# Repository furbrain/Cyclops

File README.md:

# Cyclops

Cave surveying with a camera and IMU. Under development

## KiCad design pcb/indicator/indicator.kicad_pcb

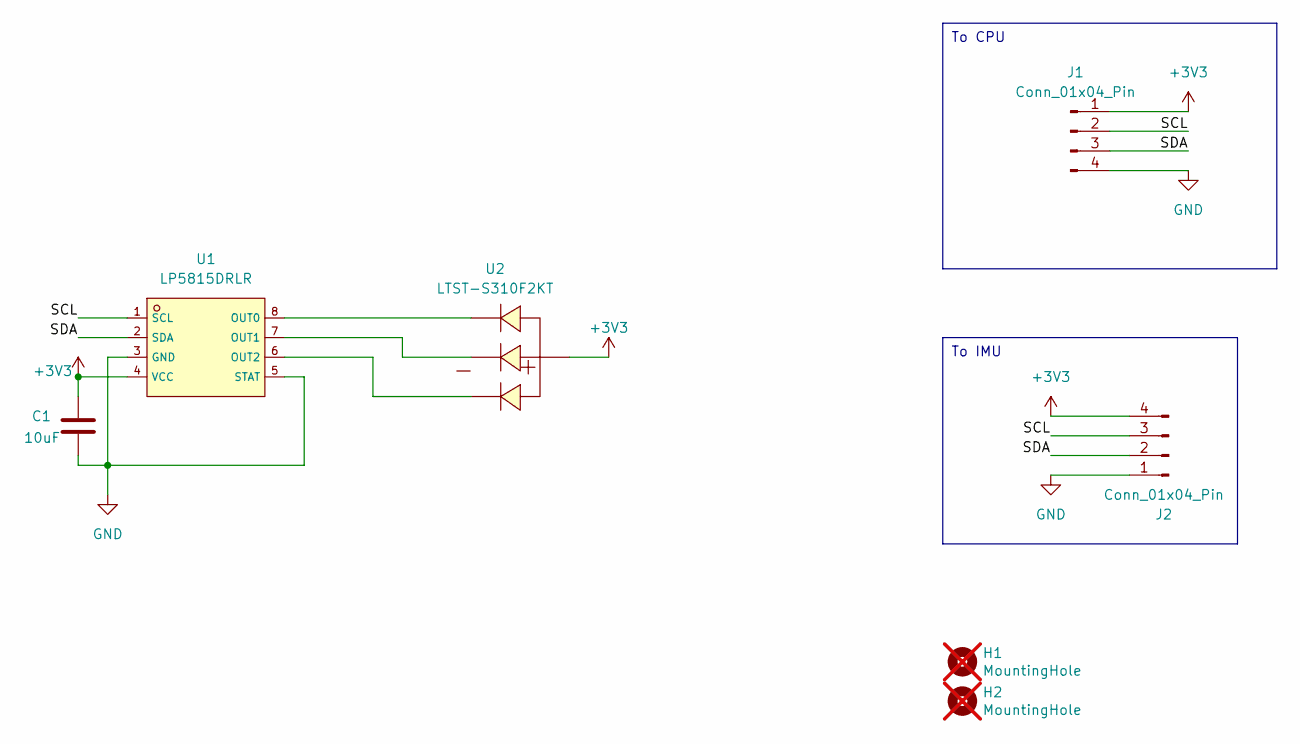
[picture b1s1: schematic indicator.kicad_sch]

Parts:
C1: 10uF; C_0805_2012Metric; JLCPCB C117956
H1, H2: MountingHole; MountingHole_3.2mm_M3; Part Description M2.5 mounting hole; not fitted
J1, J2: Conn_01x04_Pin; JUSHUO_AFA07-S04FCA-00_1x4-1MP_P1.0mm_Horizontal; JLCPCB C262710
U1: LP5815DRLR; SOT-583-8_L2.1-W1.2-P0.50-LS1.6-BL; JLCPCB C47262831
U2: LTST-S310F2KT; LED-SMD_4P-L3.2-W1.5_LTST-S310F2KT; JLCPCB C284950

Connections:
+3V3: C1.1, J1.1, J2.4, U1.4 (VCC), U2.4 (A)
/SCL: J1.2, J2.3, U1.1 (SCL)
/SDA: J1.3, J2.2, U1.2 (SDA)
GND: C1.2, J1.4, J2.1, U1.3 (GND), U1.5 (STAT)
unnamed: U1.8 (OUT0), U2.1 (C1)
unnamed: U1.7 (OUT1), U2.2 (C2)
unnamed: U1.6 (OUT2), U2.3 (C3)

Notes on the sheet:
To CPU
To IMU

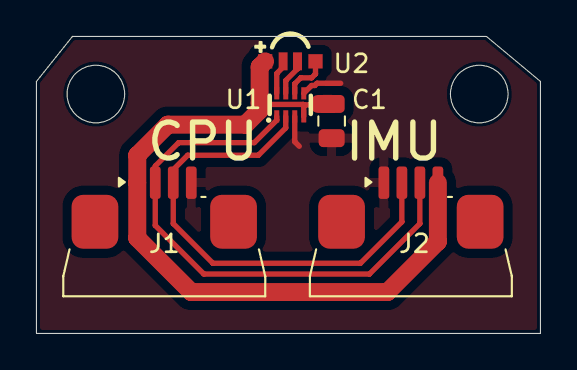
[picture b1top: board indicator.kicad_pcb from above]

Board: 2 copper layers, 28.0 x 16.5 mm, 7 parts (0 on the bottom side), 7 nets.

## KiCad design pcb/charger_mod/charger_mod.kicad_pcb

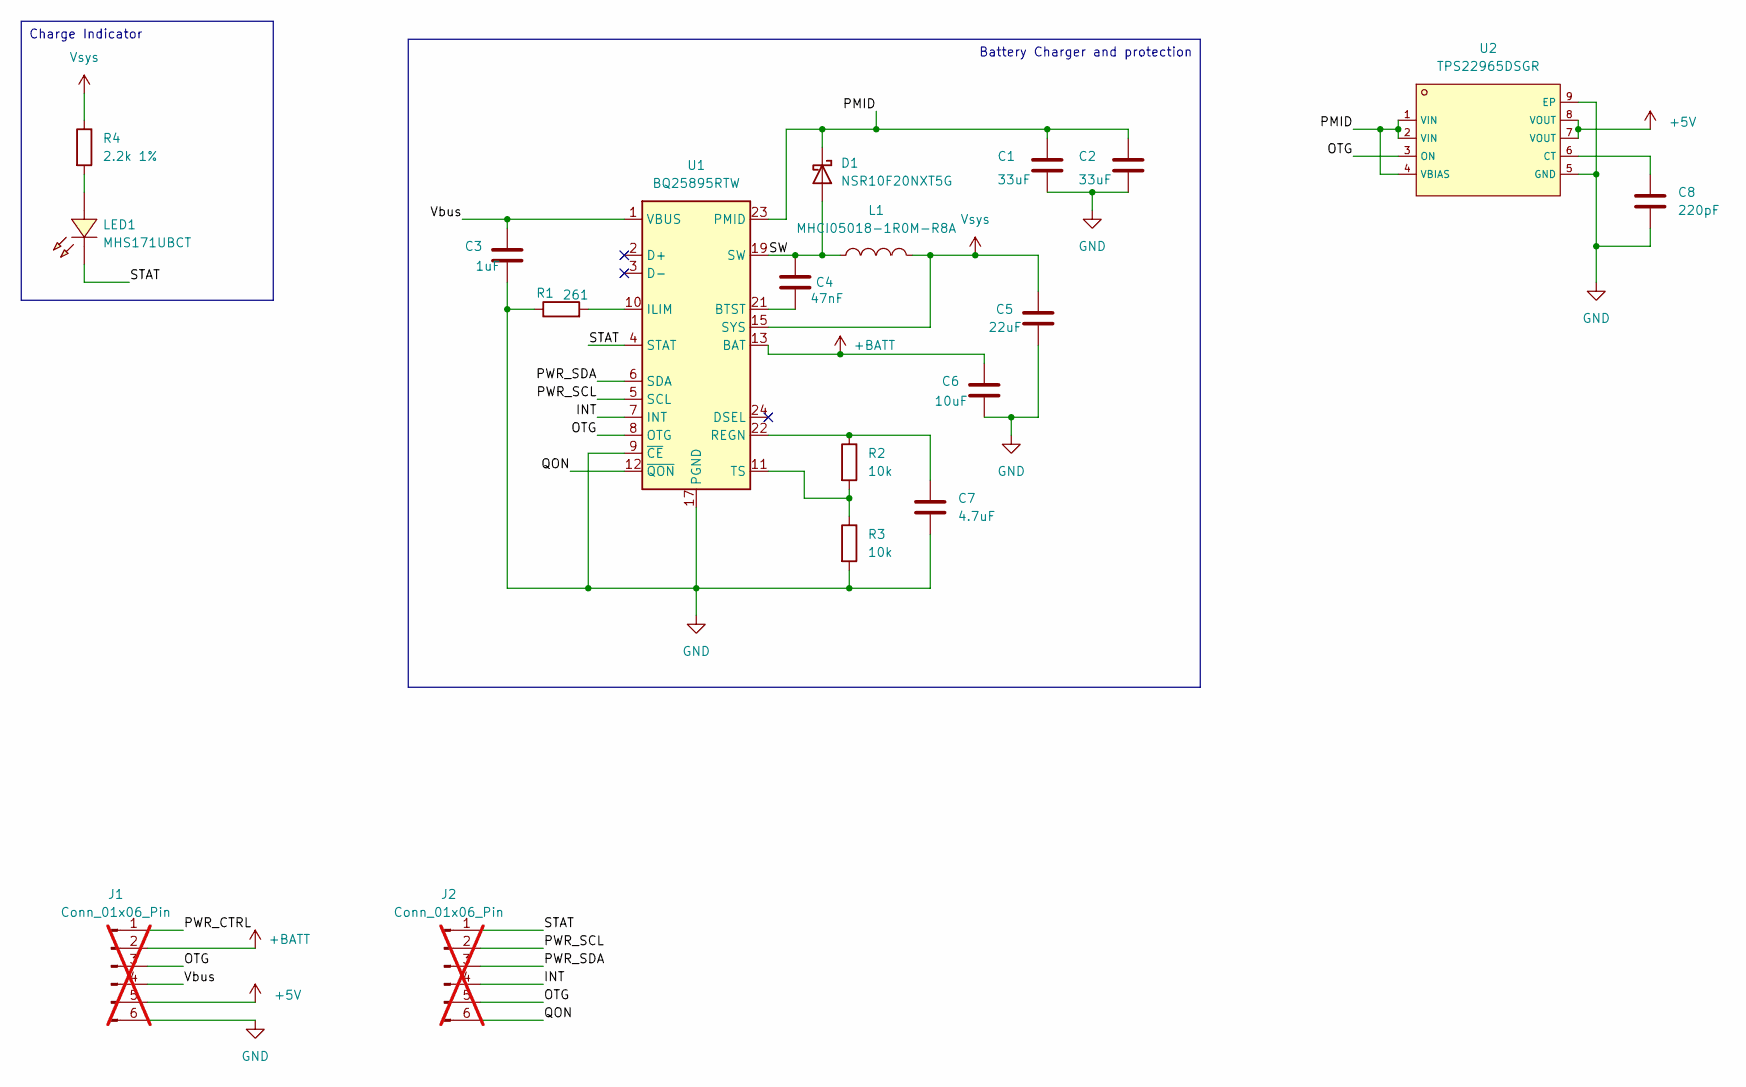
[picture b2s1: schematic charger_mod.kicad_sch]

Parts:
C1, C2: 33uF; C_1206_3216Metric; LCSC PN C76658
C3: 1uF; C_0603_1608Metric; LCSC PN C1592
C4: 47nF; C_0402_1005Metric; LCSC PN C106260
C5: 22uF; C_0805_2012Metric; LCSC PN C45783
C6: 10uF; C_0805_2012Metric; LCSC PN C117956
C7: 4.7uF; C_0603_1608Metric; LCSC PN C19666
C8: 220pF; C_0402_1005Metric; JLCPCB C1530
D1: NSR10F20NXT5G; Nexperia_DSN1608-2_1.6x0.8mm; LCSC PN C893809
J1, J2: Conn_01x06_Pin; PinHeader_1x06_P2.54mm_Vertical; not fitted
L1: MHCI05018-1R0M-R8A; IND-SMD_L5.7-W5.4; LCSC PN C329539
LED1: MHS171UBCT; LED-SMD_L2.1-W1.0-R-RD; LCSC PN C693906
R1: 261; R_0402_1005Metric; LCSC PN C25097
R2, R3: 10k; R_0402_1005Metric; LCSC PN C25744
R4: 2.2k 1%; R_0402_1005Metric; LCSC PN C25879
U1: BQ25895RTW; Texas_RTW_WQFN-24-1EP_4x4mm_P0.5mm_EP2.7x2.7mm_ThermalVias; LCSC PN C80200
U2: TPS22965DSGR; UDFN-8_L2.0-W2.0-P0.50-TL-EP; LCSC C122837

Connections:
+5V: J1.5, U2.7 (VOUT), U2.8 (VOUT)
+BATT: C6.1, J1.2, U1.13 (BAT), U1.14 (BAT)
/INT: J2.4, U1.7 (INT)
/OTG: J1.3, J2.5, U1.8 (OTG), U2.3 (ON)
/PMID: C1.1, C2.1, D1.1 (K), U1.23 (PMID), U2.1 (VIN), U2.2 (VIN), U2.4 (VBIAS)
/PWR_CTRL: J1.1
/PWR_SCL: J2.2, U1.5 (SCL)
/PWR_SDA: J2.3, U1.6 (SDA)
/QON: J2.6, U1.12 (~QON)
/STAT: J2.1, LED1.2 (K), U1.4 (STAT)
/SW: C4.1, D1.2 (A), L1.1, U1.19 (SW), U1.20 (SW)
/Vbus: C3.1, J1.4, U1.1 (VBUS)
GND: C1.2, C2.2, C3.2, C5.2, C6.2, C7.2, C8.2, J1.6, R1.1, R3.2, U1.9 (~CE), U1.17 (PGND), U1.18 (PGND), U1.25 (PGND), U2.5 (GND), U2.9 (EP)
unnamed: LED1.1 (A), R4.2
unnamed: C4.2, U1.21 (BTST)
unnamed: R1.2, U1.10 (ILIM)
unnamed: C7.1, R2.1, U1.22 (REGN)
unnamed: R2.2, R3.1, U1.11 (TS)
unnamed: C8.1, U2.6 (CT)
Vsys: C5.1, L1.2, R4.1, U1.15 (SYS), U1.16 (SYS)

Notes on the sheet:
Battery Charger and protection
Charge Indicator

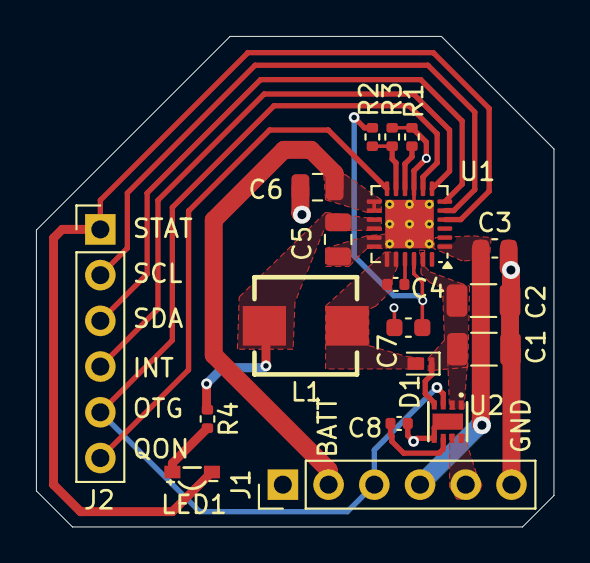
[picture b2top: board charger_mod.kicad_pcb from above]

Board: 2 copper layers, 28.8 x 27.2 mm, 19 parts (0 on the bottom side), 19 nets.

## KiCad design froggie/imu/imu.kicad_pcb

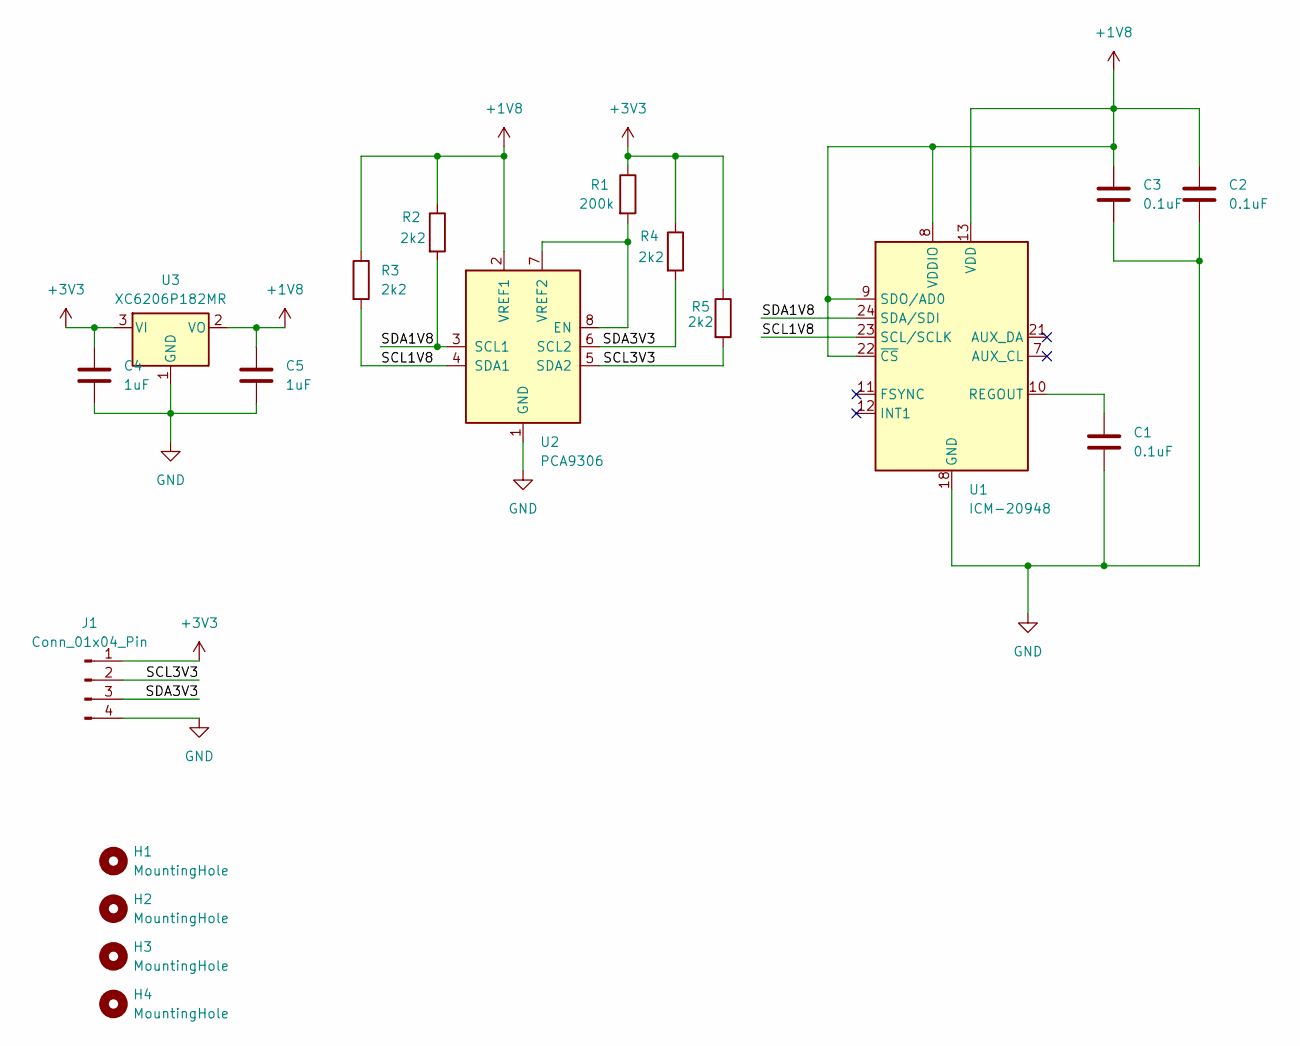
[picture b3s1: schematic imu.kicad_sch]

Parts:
C1, C2, C3: 0.1uF; C_0402_1005Metric
C4, C5: 1uF; C_0402_1005Metric
H1, H2, H3, H4: MountingHole; MountingHole_2.2mm_M2
J1: Conn_01x04_Pin; JUSHUO_AFA07-S04FCA-00_1x4-1MP_P1.0mm_Horizontal; JLCPCB C262710
R1: 200k; R_0402_1005Metric
R2, R3, R4, R5: 2k2; R_0402_1005Metric
U1: ICM-20948; InvenSense_QFN-24_3x3mm_P0.4mm
U2: PCA9306; VSSOP-8_2.3x2mm_P0.5mm
U3: XC6206P182MR; SOT-23-3; JLCPCB No C21659

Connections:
+1V8: C2.1, C3.1, C5.1, R2.1, R3.1, U1.8 (VDDIO), U1.9 (SDO/AD0), U1.13 (VDD), U1.22 (~CS), U2.2 (VREF1), U3.2 (VO)
+3V3: C4.1, J1.1, R1.1, R4.1, R5.1, U3.3 (VI)
/SCL1V8: R3.2, U1.23 (SCL/SCLK), U2.4 (SDA1)
/SCL3V3: J1.2, R5.2, U2.5 (SDA2)
/SDA1V8: R2.2, U1.24 (SDA/SDI), U2.3 (SCL1)
/SDA3V3: J1.3, R4.2, U2.6 (SCL2)
GND: C1.2, C2.2, C3.2, C4.2, C5.2, J1.4, U1.18 (GND), U1.20 (GND), U2.1 (GND), U3.1 (GND)
unnamed: C1.1, U1.10 (REGOUT)
unnamed: R1.2, U2.7 (VREF2), U2.8 (EN)

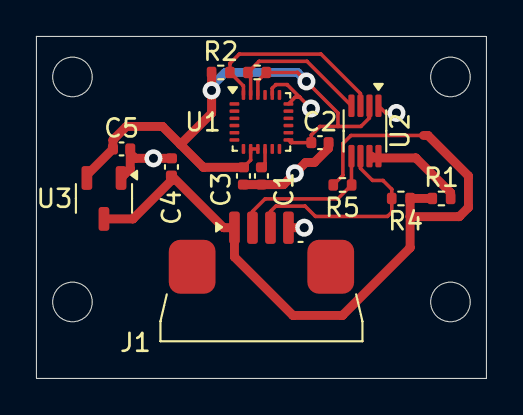
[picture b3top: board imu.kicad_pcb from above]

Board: 2 copper layers, 25.0 x 19.0 mm, 18 parts (0 on the bottom side), 9 nets.

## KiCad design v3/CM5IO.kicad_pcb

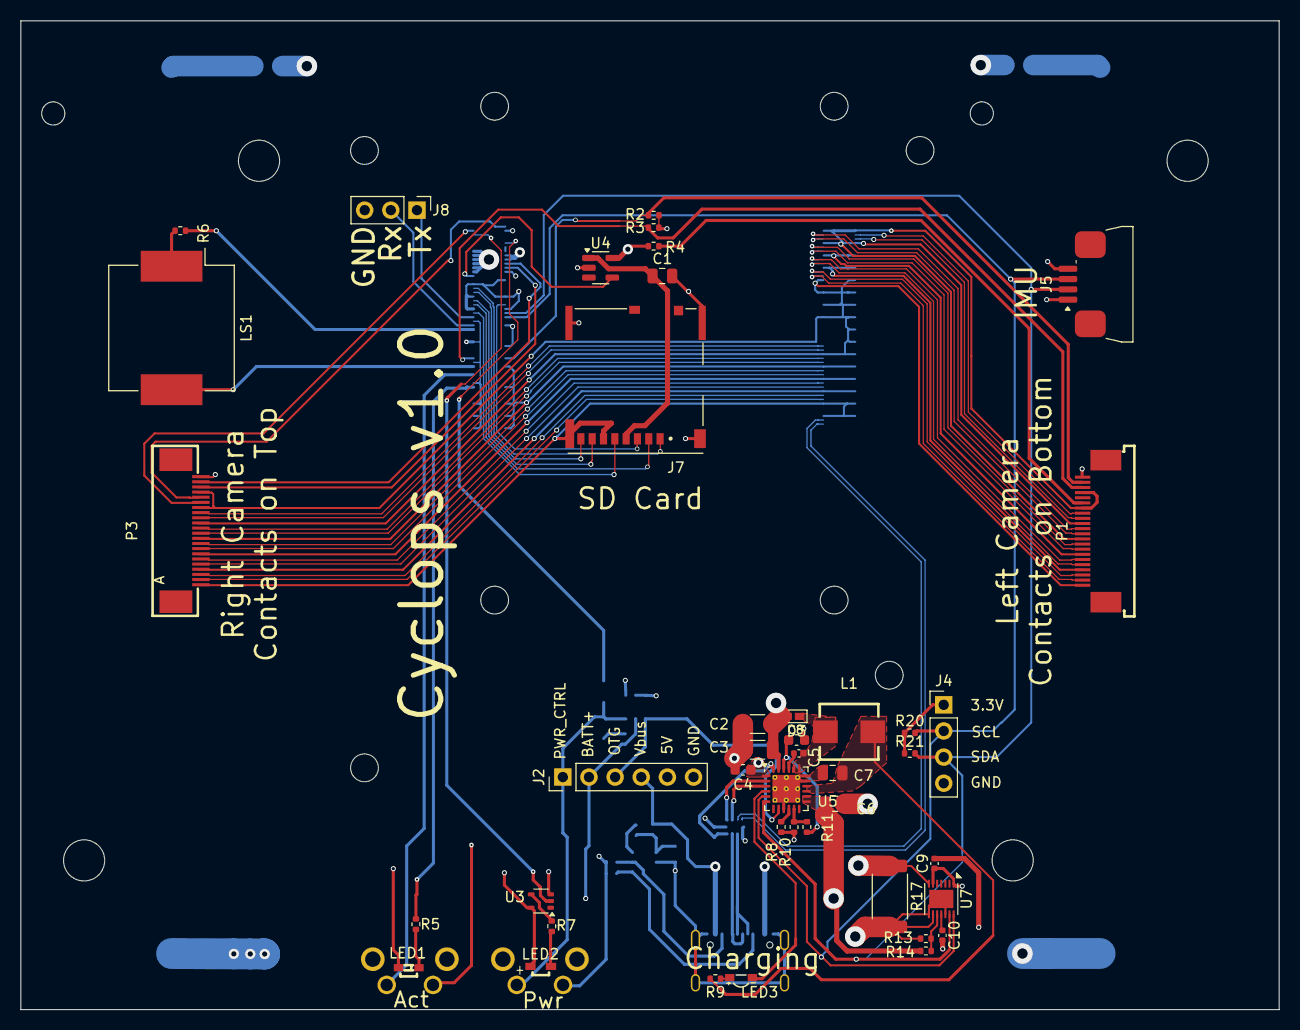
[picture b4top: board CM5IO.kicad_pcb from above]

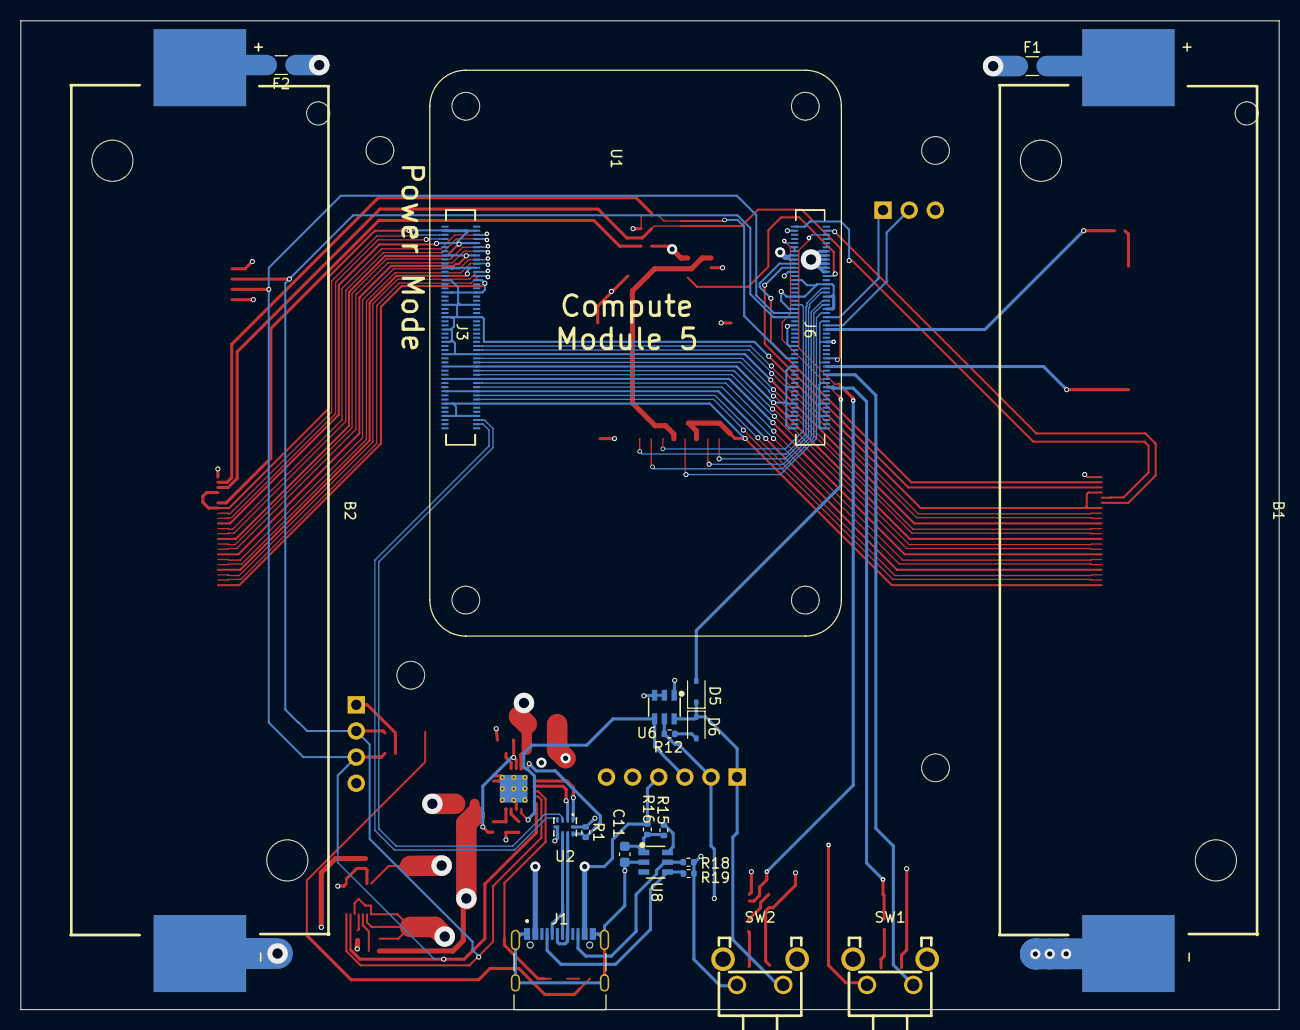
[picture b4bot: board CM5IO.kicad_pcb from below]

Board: 4 copper layers, 122.3 x 96.1 mm, 68 parts (22 on the bottom side), 82 nets.

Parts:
B1, B2: BH-21700-B1BJ001; BAT-SMD_L82.5.5-W25-BH-21700-B1BJ001
C1, C7: 10uF; C_0805_2012Metric
C2, C3: 33uF; C_1206_3216Metric
C4, C11: 1uF; C_0603_1608Metric
C5: 47nF; C_0402_1005Metric
C6: 22uF; C_0805_2012Metric
C8: 4.7uF; C_0603_1608Metric
C9: 100nF; C_0402_1005Metric
C10: 470nF; C_0402_1005Metric
D3: NSR10F20NXT5G; Nexperia_DSN1608-2_1.6x0.8mm
D5, D6: D_Schottky; D_SOD-323
F1, F2: Fuse; Fuse_1206_3216Metric
H1, H2, H3, H4: MountingHole; MountingHole_2.7mm_M2.5_DIN965
J1: TYPE-C-31-M-12; HRO_TYPE-C-31-M-12
J2: Conn_01x06_Pin; PinHeader_1x06_P2.54mm_Vertical
J3, J6: 10164227-1001A1RLF; CM5_connector
J4: Conn_01x04_Pin; PinHeader_1x04_P2.54mm_Vertical
J5: Conn_01x04_Pin; JUSHUO_AFA07-S04FCA-00_1x4-1MP_P1.0mm_Horizontal
J7: Micro_SD_Card_Det; SDCARD_MOLEX_503398-1892
J8: UART Connection; PinHeader_1x03_P2.54mm_Vertical
L1: MHCI05018-1R0M-R8A; IND-SMD_L5.7-W5.4
LED1: MHS171CYCT; LED-SMD_L2.0-W1.1-R-RD-SIDE_YELLOW
LED2: MHS171UGCT; LED-SMD_L2.0-W1.1_RD_GREEN_SIDE
LED3: MHS171UBCT; LED-SMD_L2.1-W1.0-R-RD
LS1: KMTG1203; Buzzer_Mallory_AST1240MLQ
P1: AFC07-S22FCC-00 (Bottom contact); FPC-SMD_AFC07-S22FCC-00
P3: FPC_0_5MM_22P_Pull_type_H2_0mm_Pick_up; FPC-SMD_P0.50-22P_LSSJ-H2.0-22P
R1, R10, R11, R12, R15: 10k; R_0402_1005Metric
R2, R3, R4, R20, R21: 2.2K 1%; R_0402_1005Metric
R5, R7, R16: 1k; R_0402_1005Metric
R6: 180; R_0402_1005Metric
R8: 261; R_0402_1005Metric
R9: 2.2k 1%; R_0402_1005Metric
R13: 300k; R_0402_1005Metric
R14: 200k; R_0402_1005Metric
R17: 10mOhm; R_2512_6332Metric
R18, R19: 5.1k; R_0402_1005Metric
SW1: TS-1093C-A14B3-D1; SW-TH_TS-1093C-A14B3-D1
SW2: TS-1093C-A5B3-D1; SW-TH_TS-1093C-A5B3-D1
U1: Raspberry-Pi-5-Compute-Module
U2: TS3USB221ARSER; UQFN-10_L2.0-W1.5-P0.50-BL
U3: 74LVC1G07SE-7; SOT-353_SC-70-5
U4: RT9742GGJ5; SOT-23-5
U5: BQ25895RTW; Texas_RTW_WQFN-24-1EP_4x4mm_P0.5mm_EP2.7x2.7mm_ThermalVias
U6: SN74LVC1G57DBVR; SOT-23-6_L2.9-W1.6-P0.95-LS2.8-BL
U7: MAX17261xxTD; TDFN-14-1EP_3x3mm_P0.4mm_EP1.78x2.35mm
U8: CH221K; SOT-23-6_L2.9-W1.6-P0.95-LS2.8-BL-2

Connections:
+BATT: C7.1, C9.1, F1.1, F2.1, J2.2, R12.1, R13.1, U5.13 (BAT), U5.14 (BAT), U6.5 (VCC), U7.1 (TH), U7.6 (BATT)
-BATT: B1.2, B2.2, C9.2, C10.2, R14.2, R17.2, U7.8 (GND), U7.9 (CSPL), U7.12 (ALRT), U7.15 (GND)
/+3.3v: J4.1, J5.4, J6.78 (GPIO_VREF(1.8v/3.3v_Input)), J6.84 (+3.3v_(Output)), J6.86 (+3.3v_(Output)), LED1.1 (K), LED2.1 (+), P1.1, P3.1, R1.1, R2.1, R3.1, R4.1, R20.1, R21.1, U2.10 (VCC), U3.5 (VCC), U4.5 (IN), U6.1 (IN1)
/CC1: J1.A5 (CC1), R19.1, U8.4 (CC1)
/CC2: J1.B5 (CC2), R18.2, U8.5 (CC2)
/CM5_5V: C2.1, C3.1, D3.1 (K), J2.5, J6.77 (+5v_(Input)), J6.79 (+5v_(Input)), J6.81 (+5v_(Input)), J6.83 (+5v_(Input)), J6.85 (+5v_(Input)), J6.87 (+5v_(Input)), U5.23 (PMID)
/CM5_GPIO ( Ethernet, GPIO, SDCARD)/+1.8v: J6.88 (+1.8v_(Output)), J6.90 (+1.8v_(Output))
/CM5_GPIO ( Ethernet, GPIO, SDCARD)/BUTTON: J6.27 (GPIO20), SW1.2
/CM5_GPIO ( Ethernet, GPIO, SDCARD)/BUZZ_A: J6.49 (GPIO18), R6.1
/CM5_GPIO ( Ethernet, GPIO, SDCARD)/BUZZ_B: J6.31 (GPIO12), LS1.2
/CM5_GPIO ( Ethernet, GPIO, SDCARD)/CAM_GPIO0: J6.97 (CAM_GPIO0), P3.6
/CM5_GPIO ( Ethernet, GPIO, SDCARD)/CAM_GPIO1: J6.100 (CAM_GPIO1), P3.5
/CM5_GPIO ( Ethernet, GPIO, SDCARD)/GPIO14: J6.55 (GPIO14), J8.1
/CM5_GPIO ( Ethernet, GPIO, SDCARD)/GPIO15: J6.51 (GPIO15), J8.2
/CM5_GPIO ( Ethernet, GPIO, SDCARD)/ID_SC: J6.35 (ID_SC), P1.3, R3.2
/CM5_GPIO ( Ethernet, GPIO, SDCARD)/ID_SD: J6.36 (ID_SD), P1.2, R2.2
/CM5_GPIO ( Ethernet, GPIO, SDCARD)/SD_CLK: J6.57 (SD_CLK), J7.5 (CLK)
/CM5_GPIO ( Ethernet, GPIO, SDCARD)/SD_CMD: J6.62 (SD_CMD), J7.3 (CMD)
/CM5_GPIO ( Ethernet, GPIO, SDCARD)/SD_DAT0: J6.63 (SD_DAT0), J7.7 (DAT0)
/CM5_GPIO ( Ethernet, GPIO, SDCARD)/SD_DAT1: J6.67 (SD_DAT1), J7.8 (DAT1)
/CM5_GPIO ( Ethernet, GPIO, SDCARD)/SD_DAT2: J6.69 (SD_DAT2), J7.1 (DAT2)
/CM5_GPIO ( Ethernet, GPIO, SDCARD)/SD_DAT3: J6.61 (SD_DAT3), J7.2 (DAT3/CD)
/CM5_GPIO ( Ethernet, GPIO, SDCARD)/SD_PWR: C1.1, J7.4 (VDD), U4.1 (OUT)
/CM5_GPIO ( Ethernet, GPIO, SDCARD)/SD_PWR_ON: J6.75 (SD_PWR_ON), U4.4 (EN)
/CM5_GPIO ( Ethernet, GPIO, SDCARD)/nPWR_LED: J6.95 (LED_nPWR), U3.2
/CM5_HighSpeed/DPHY0_C_N: J3.27 (MIPI0_C_N), P3.15
/CM5_HighSpeed/DPHY0_C_P: J3.29 (MIPI0_C_P), P3.14
/CM5_HighSpeed/DPHY0_D0_N: J3.15 (MIPI0_D0_N), P3.21
/CM5_HighSpeed/DPHY0_D0_P: J3.17 (MIPI0_D0_P), P3.20
/CM5_HighSpeed/DPHY0_D1_N: J3.21 (MIPI0_D1_N), P3.18
/CM5_HighSpeed/DPHY0_D1_P: J3.23 (MIPI0_D1_P), P3.17
/CM5_HighSpeed/DPHY0_D2_N: J3.33 (MIPI0_D2_N), P3.12
/CM5_HighSpeed/DPHY0_D2_P: J3.35 (MIPI0_D2_P), P3.11
/CM5_HighSpeed/DPHY0_D3_N: J3.39 (MIPI0_D3_N), P3.9
/CM5_HighSpeed/DPHY0_D3_P: J3.41 (MIPI0_D3_P), P3.8
/CM5_HighSpeed/DPHY1_C_N: J3.87 (MIPI1_C_N), P1.15
/CM5_HighSpeed/DPHY1_C_P: J3.89 (MIPI1_C_P), P1.14
/CM5_HighSpeed/DPHY1_D0_N: J3.75 (MIPI1_D0_N), P1.21
/CM5_HighSpeed/DPHY1_D0_P: J3.77 (MIPI1_D0_P), P1.20
/CM5_HighSpeed/DPHY1_D1_N: J3.81 (MIPI1_D1_N), P1.18
/CM5_HighSpeed/DPHY1_D1_P: J3.83 (MIPI1_D1_P), P1.17
/CM5_HighSpeed/DPHY1_D2_N: J3.93 (MIPI1_D2_N), P1.12
/CM5_HighSpeed/DPHY1_D2_P: J3.95 (MIPI1_D2_P), P1.11
/CM5_HighSpeed/DPHY1_D3_N: J3.94 (MIPI1_D3_N), P1.9
/CM5_HighSpeed/DPHY1_D3_P: J3.96 (MIPI1_D3_P), P1.8
/CM5_HighSpeed/SCL0: J6.80 (SCL0), P3.3
/CM5_HighSpeed/SDA0: J6.82 (SDA0), P3.2
/CM5_USB2_N: J3.3 (USB2_N), U2.4 (2D-)
/CM5_USB2_P: J3.5 (USB2_P), U2.3 (2D+)
/DSEL: R1.2, U2.9 (S), U5.24 (DSEL)
/PWR_BUT: D5.2 (A), J6.92 (PWR_BUT)
/PWR_D+: U2.1 (1D+), U5.2 (D+)
/PWR_D-: U2.2 (1D-), U5.3 (D-)
/PWR_SCL: J4.2, J5.3, J6.56 (GPIO3), R20.2, U5.5 (SCL), U7.14 (SCL)
/PWR_SDA: J4.3, J5.2, J6.58 (GPIO2), R21.2, U5.6 (SDA), U7.13 (SDA)
/Power/OTG: J2.3, U5.8 (OTG), U6.4 (Y)
/Power/PWR_CTRL: D5.1 (K), D6.1 (K), J2.1, SW2.2, U6.6 (IN2)
/Power/STAT: LED3.2 (K), U5.4 (STAT)
/Power/SW: C5.1, D3.2 (A), L1.1, U5.19 (SW), U5.20 (SW)
/USB2_N: J1.A7 (DN1), J1.B7 (DN2), U2.7 (D-)
/USB2_P: J1.A6 (DP1), J1.B6 (DP2), U2.8 (D+)
/Vbus: C4.1, J1.A4_B9 (VBUS), J1.B4_A9 (VBUS), J2.4, R16.1, U5.1 (VBUS)
GND: C1.2, C2.2, C3.2, C4.2, C6.2, C7.2, C8.2, C11.2, J1.A1_B12 (GND), J1.B1_A12 (GND), J1.S1 (SHIELD), J1.S2 (SHIELD), J1.S3 (SHIELD), J1.S4 (SHIELD), J2.6, J3.7 (GND), J3.8 (GND), J3.13 (GND), J3.14 (GND), J3.19 (GND), J3.20 (GND), J3.25 (GND), J3.26 (GND), J3.31 (GND), J3.32 (GND), J3.37 (GND), J3.38 (GND), J3.44 (GND), J3.50 (GND), J3.55 (GND), J3.56 (GND), J3.61 (GND), J3.62 (GND), J3.67 (GND), J3.68 (GND), J3.73 (GND), J3.74 (GND), J3.79 (GND), J3.80 (GND), J3.85 (GND), J3.86 (GND), J3.91 (GND), J3.92 (GND), J3.97 (GND), J3.98 (GND), J4.4, J5.1, J6.1 (GND), J6.2 (GND), J6.7 (GND), J6.8 (GND), J6.13 (GND), J6.14 (GND), J6.22 (GND), J6.23 (GND), J6.32 (GND), J6.33 (GND), J6.42 (GND), J6.43 (GND), J6.52 (GND), J6.53 (GND), J6.59 (GND), J6.60 (GND), J6.65 (GND), J6.66 (GND), J6.71 (GND), J6.74 (GND), J6.98 (GND), J7.6 (VSS), J7.11 (SHIELD), J8.3, P1.4, P1.7, P1.10, P1.13, P1.16, P1.19, P1.22, P3.4, P3.7, P3.10, P3.13, P3.16, P3.19, P3.22, R8.1, R11.2, R17.1, R18.1, R19.2, SW1.1, SW2.1, U2.5 (GND), U2.6 (OE#), U3.3 (GND), U4.2 (GND), U5.9 (~CE), U5.17 (PGND), U5.18 (PGND), U5.25 (PGND), U6.2 (GND), U6.3 (IN0), U7.7 (CSN), U8.2 (GND)
unnamed: B1.1, F1.2
unnamed: B2.1, F2.2
unnamed: D6.2 (A), R12.2
unnamed: J6.21 (LED_nACT), R5.2
unnamed: LED1.2 (A), R5.1
unnamed: LED2.2 (-), R7.1
unnamed: LED3.1 (A), R9.2
unnamed: LS1.1, R6.2
unnamed: P1.6, R4.2
unnamed: R7.2, U3.4
unnamed: C5.2, U5.21 (BTST)
unnamed: R8.2, U5.10 (ILIM)
unnamed: C8.1, R10.1, U5.22 (REGN)
unnamed: R10.2, R11.1, U5.11 (TS)
unnamed: R13.2, R14.1, U7.10 (CELLX)
unnamed: C10.1, U7.11 (REG)
unnamed: R15.2, U8.6 (CFG)
unnamed: C11.1, R15.1, R16.2, U8.1 (VDD)
Vsys: C6.1, L1.2, R9.1, U5.15 (SYS), U5.16 (SYS)

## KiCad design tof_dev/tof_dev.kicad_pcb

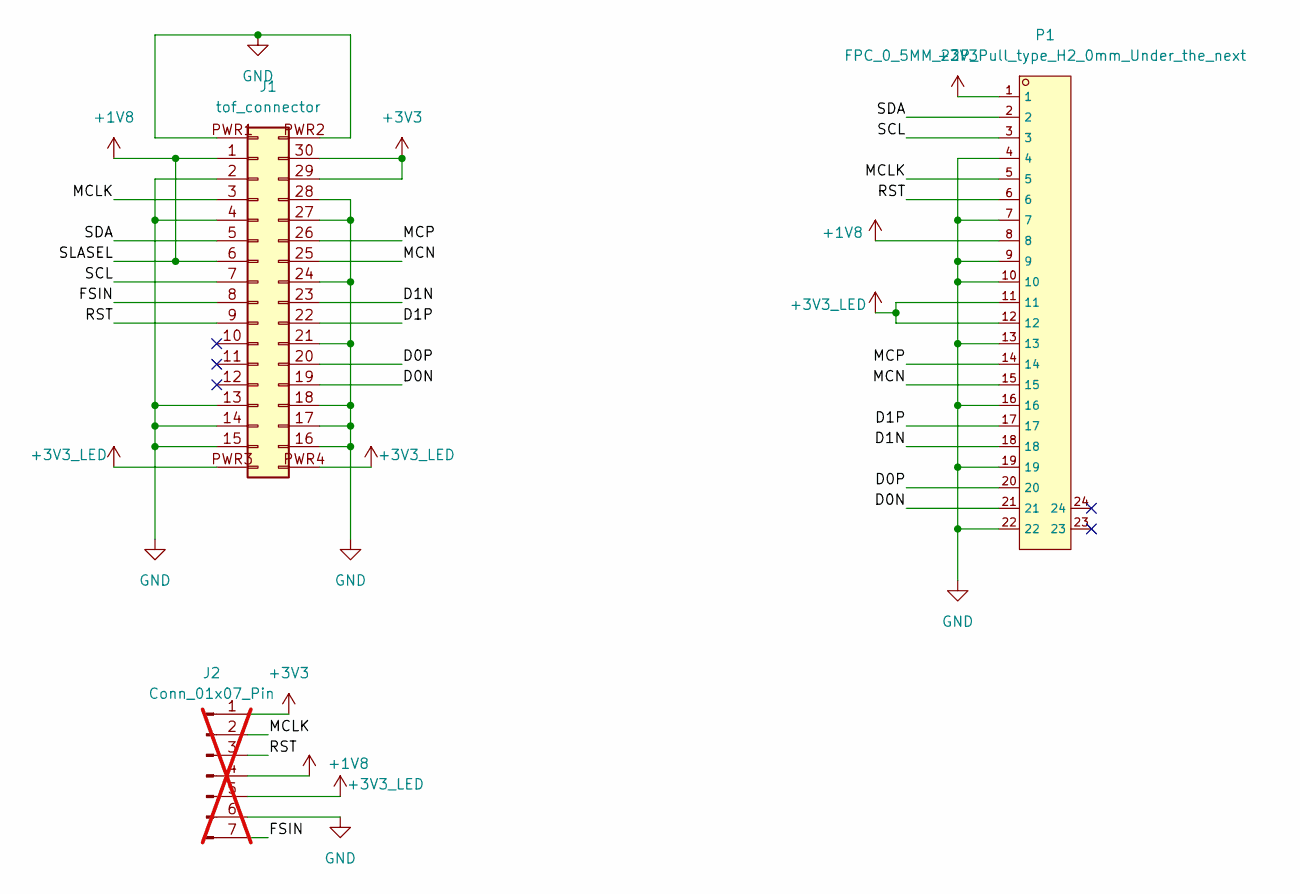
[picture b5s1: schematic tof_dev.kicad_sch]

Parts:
J1: tof_connector; tof; LCSC C50087636
J2: Conn_01x07_Pin; PinHeader_1x07_P2.54mm_Vertical; not fitted
P1: FPC_0_5MM_22P_Pull_type_H2_0mm_Under_the_next; FPC-SMD_AFC07-S22FCC-00; LCSC C11056

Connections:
+1V8: J1.1, J1.6, J2.4, P1.8
+3V3: J1.29, J1.30, J2.1, P1.1
+3V3_LED: J1.PWR3 (Pwr_3), J1.PWR4 (Pwr_4), J2.5, P1.11, P1.12
/D0N: J1.19, P1.21
/D0P: J1.20, P1.20
/D1N: J1.23, P1.18
/D1P: J1.22, P1.17
/FSIN: J1.8, J2.7
/MCLK: J1.3, J2.2, P1.5
/MCN: J1.25, P1.15
/MCP: J1.26, P1.14
/RST: J1.9, J2.3, P1.6
/SCL: J1.7, P1.3
/SDA: J1.5, P1.2
GND: J1.2, J1.4, J1.13, J1.14, J1.15, J1.16, J1.17, J1.18, J1.21, J1.24, J1.27, J1.28, J1.PWR1 (Pwr_1), J1.PWR2 (Pwr_2), J2.6, P1.4, P1.7, P1.9, P1.10, P1.13, P1.16, P1.19, P1.22

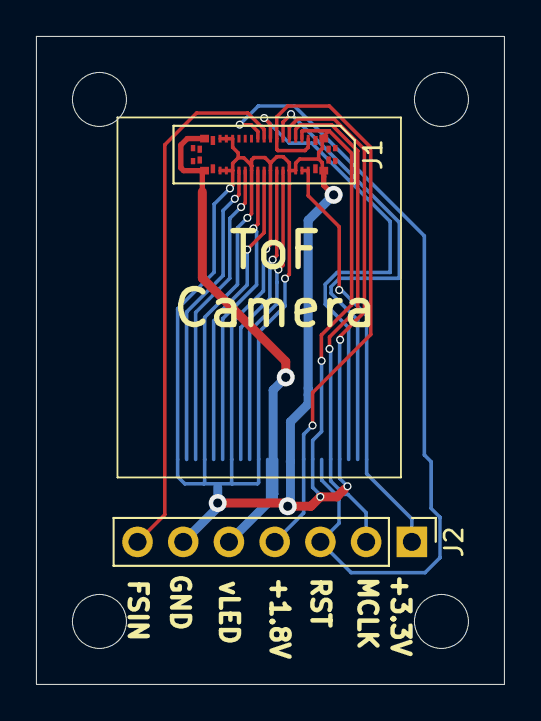
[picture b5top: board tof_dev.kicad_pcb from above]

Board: 2 copper layers, 26.0 x 36.0 mm, 3 parts (1 on the bottom side), 15 nets.

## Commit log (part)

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2024-03-09 Initial frame
2024-03-09 Add first attempt at pHAT. Note GND connected wrong
2024-03-09 Add initial python code
2024-03-09 tidying
2024-03-10 Make imu_data time sensitive, add test script
2024-03-10 Get combined video+imu_data working
2024-03-13 Various improvements
2024-05-19 recorder script with button and feedback
2024-05-19 various other bits
2024-05-19 various bits
2024-05-19 Various fixes
2024-05-19 Add reading and tracking files
2024-05-25 Make a gstreamer reader with timestamps
2024-05-26 add seek
2024-05-26 Create CyclopsReader class
2024-06-18 Experiments in quaternions
2024-08-11 Lots of updates
2024-08-24 keyframe selector code
2024-08-24 Enclosure and clips
2024-08-24 more keyframe stuff
2024-08-24 pi zero requirements doc
2024-08-24 seems to be needed?
2024-08-24 Improve mkv quality
2024-08-24 Fix bug and remove calibration from here...
2024-08-24 ignore venv
2024-08-25 Create beep server
2024-08-25 Make work via crontab
2024-08-25 find next available file, tolerate missing vid file
2024-08-26 make it beepy and fix bugs
2024-09-15 Start thinking about TOF camera
2024-09-15 playing with SLAM style tools
2024-09-16 Increase resolution of camera feed
2024-09-16 Start using TOF camera
2024-09-18 more work on TOF stuff: combined video generation working
2024-09-21 Add raw decipherment code
2024-09-21 UPdate to more condensed TOF output
2024-09-21 condense TOF output and adjust for cameras changing ID
2024-09-25 More work done!
2024-09-28 Work on cmaera registration and glitch detection process
2024-09-28 Various fettling
2024-09-28 switch to using depth mode
2024-10-04 MOre work
2024-10-26 Update gitignore
2024-10-26 Updates to TOF code
2024-10-26 Improve calibration processes, start work on dual calibration
2024-10-26 Import some stuff for the pointcloud algos
2024-10-26 Test code for to stream dual cams
2024-10-26 update streaming process
2024-10-26 Add snapshot script
2025-01-11 start work on ROS
2025-01-11 Fix memory leak in gstreamer specs
2025-01-11 Lens calibration for dual cameras
2025-01-11 Switch to using posix-ipc and semaphores
2025-01-12 various updates
2025-01-12 include Dockerfile
2025-01-12 Playing with kalman filters
2025-01-12 make more modular camera finder
2025-01-12 bug fix
2025-01-12 make runnable from cmd line
2025-01-13 add gstreamer to ros bridge with compression
2025-02-12 add ROS modules
2025-02-23 make sensors rate aware
2025-03-04 mkvbag - treat mkv like a bag file
2025-03-04 Various updates and shininess
2025-03-08 start work on ros automation
2025-03-08 Add cyclops_launch into cyclops folder
2025-03-08 Various bug fixes
2025-03-08 make recoding record everythin
2025-03-08 do happy when everythin up and running
2025-03-08 Add activity monitor
2025-03-08 various work
2025-03-08 get startup detection working
2025-03-09 General tidy up. All old stuff kept in branch gstreamer_mkv
2025-03-16 Add more launch files
2025-03-17 Get depth filling code working
2025-03-24 Add OpenCL to Dockerfile, for radxa
2025-04-06 more work on aarch64
2025-04-06 ignore catkin build bits
2025-05-29 more stuff
2025-05-29 Various ROS stuff
2025-05-29 docker updates
2025-08-25 switching to ROS2
2025-09-07 update cyclops
2025-09-07 Add interface for calibration action
2025-09-07 add tof camera code
2025-09-07 add web interface
2025-09-09 Get lens calibration working: DONE
2025-09-12 Get web calibration working for camera and camera - camera
2025-09-13 Proper docker installation fro kalibr
2025-09-15 get 3d viewer working with point clouds and markers
2025-09-24 get cameras sync'd
2025-10-08 start work on beeper
2025-10-08 faster depth registration in python
2025-10-08 faster depth registration in C++
2025-10-08 orb make settings and various other work
2025-10-10 Create Beep messages and Beep server
2025-10-10 Add ROS2 beeper
2025-10-12 Add beep_server to systemd
2025-10-14 Add mode switcher
2025-10-14 Make ros3djs viewers dynamic
2025-10-14 turn on/off subsystems depending on web page
2025-10-16 enhance smartnode to include graceful shutdown
2025-10-16 incorporate rectify and get launch files working
2025-10-16 add home screen and capture pane separately
2025-11-16 Fixing calibration procedures
2025-11-16 Get working with ORB
2025-11-23 Refactor index.html to be more modular and work with flask
2025-11-23 Record bags in capture mode
2025-11-23 Add ROS node to initiate model extraction
2025-11-23 Work on PLY viewer
2025-11-25 make modeller behave nicely on shutdown
2025-11-25 Get modeller interacting with browser
2025-11-26 directory fettling before and after capture implemented
2025-11-26 various fixes fro recording pane
2025-11-28 add gunicorn and ros services
2025-11-28 add button monitor to start and stop capture on button press
2025-11-30 Add networkmanager file for AP
2025-11-30 Add downloads and PLY viewer to recordings pane
2026-01-02 New PCB
2026-01-02 Various work on ROS stuff
2026-01-02 stecksconf talk!
2026-01-02 Various pcb mods
2026-02-21 convert to CS20 TOF
2026-02-27 add various models
2026-03-20 various updates pt 1
2026-03-20 gunicorn stuff
2026-03-20 various web stuff
2026-03-20 model making scripts
2026-03-20 various launch changes
2026-03-20 add frog case
2026-03-24 switch over to binocular views
2026-04-15 various bits and bobs to make stereo work
2026-04-18 battery holder
2026-04-18 case designs
2026-04-19 adding power management to board
2026-04-22 Finalise v1.0 design
2026-05-24 add battery monitor node
2026-06-02 add tof development board
2026-06-02 storign various old hardware changes
2026-06-02 add clip-on case
2026-06-02 update install.md file
2026-06-04 add correct pins for beep server
2026-06-04 Add slideshow to web API
2026-06-04 switch to ICM20948 jobbie
2026-06-04 add 5th distortion coefficient
2026-06-04 updated hardware files
2026-06-04 Create charger mod board
2026-06-04 imu board
2026-06-04 calibration patterns and other oddments
2026-06-04 create hardware for vertex
2026-06-04 add launch files to include battery, CPU and mem info
2026-06-04 add process memory monitor
2026-06-04 Remove unused ROS1 and docker files
2026-06-04 Move main pcb from v3 to proper pcb dir, and rename from CM5IO to main
2026-06-04 move charger module and imu pcbs to pcb dir
2026-06-04 remove unused hardware dir
2026-06-04 move enclosure files into dedicated directory
2026-06-04 remove unused files
2026-06-04 remove unneeded files
2026-06-11 One shot download and make model
2026-06-11 FIx plug design
2026-06-11 add pin button and starts of bq25895 code
2026-06-11 aggressively reduce exposure to reduce motion blur
2026-06-12 More robust (and simpler) camera launch
2026-06-23 fix shutter speed and max gain
2026-06-23 boost gamma
2026-06-24 update to latest iteration of ORB_SLAM3
2026-06-24 Create indicator module
2026-06-24 Add code to make diffraction lens
2026-06-24 Add lightburn file for diffraction grating
2026-06-24 minor bug fixes
